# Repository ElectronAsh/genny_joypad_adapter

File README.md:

# genny_joypad_adapter
Genesis / MD joypad adapter for old-skool computers and consoles.

WARNING: Please do not use this adapter yet!

It's still a work-in-progress, and damage may occur to both the console / computer and the joypad.

The resistors should limit the maximum current on each signal pin, and it should in theory work on the "Atari style" joystick ports, 
on machines like the Atari 2600/400/800/1200/130XE/ST, Amiga, Vic 20, C64 / C64GS etc.

The diodes allow the Genesis joypad to only pull the signals LOW on the computer side.

The DIP switches are for enabling two-button support for the Atari 7800.

DIP switch 1 enables connection of pin 6, which is normally the "Fire" button on many retro machines.

DIP switches 2 and 3 allow the PNP transistors to drive pins 9 and 5 HIGH, as those are Active-High on the 7800.
Buttons B and C on the Genesis joypad can then be used as "Left Button" / "Right Button" (respectively) on the 7800.

All DIP switches should be OFF when the adapter is used with machines other than the Atari 7800.

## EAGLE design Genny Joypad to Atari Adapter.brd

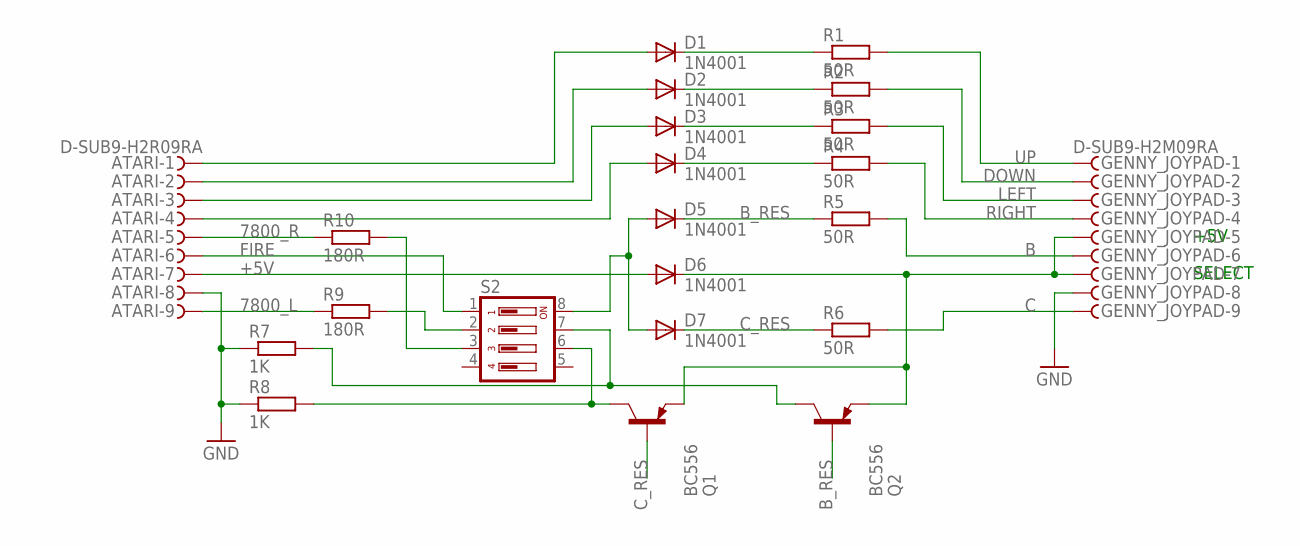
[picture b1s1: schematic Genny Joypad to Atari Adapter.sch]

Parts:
ATARI: D-SUB9-H2R09RA; H2R09RA
D1, D2, D3, D4, D5, D6, D7: 1N4001; DO35-7
GENNY_JOYPAD: D-SUB9-H2M09RA; H2M09RA
Q1, Q2: BC556; TO92-EBC
R1, R2, R3, R4, R5, R6: 50R; 0204/7
R7, R8: 1K; 0204/7
R9, R10: 180R; 0204/7
S2: DIP04YL

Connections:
7800_L: ATARI.9, R9.1
7800_R: ATARI.5, R10.1
+5V: D6.C, GENNY_JOYPAD.5, GENNY_JOYPAD.7, Q1.E, Q2.E
B: GENNY_JOYPAD.6, R5.2
B_PNP: Q2.C, R7.2, S2.7
B_RES: D5.C, Q2.B, R5.1
C: GENNY_JOYPAD.9, R6.2
C_PNP: Q1.C, R8.2, S2.6
C_RES: D7.C, Q1.B, R6.1
DOWN: GENNY_JOYPAD.2, R2.2
FIRE: D5.A, D7.A, S2.8
GND: ATARI.8, GENNY_JOYPAD.8, R7.1, R8.1
LEFT: GENNY_JOYPAD.3, R3.2
unnamed: D1.C, R1.1
unnamed: ATARI.7, D6.A
unnamed: ATARI.1, D1.A
unnamed: D2.C, R2.1
unnamed: ATARI.2, D2.A
unnamed: D3.C, R3.1
unnamed: ATARI.3, D3.A
unnamed: D4.C, R4.1
unnamed: ATARI.4, D4.A
unnamed: ATARI.6, S2.1
unnamed: R9.2, S2.2
unnamed: R10.2, S2.3
RIGHT: GENNY_JOYPAD.4, R4.2
UP: GENNY_JOYPAD.1, R1.2

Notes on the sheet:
+5V
SELECT

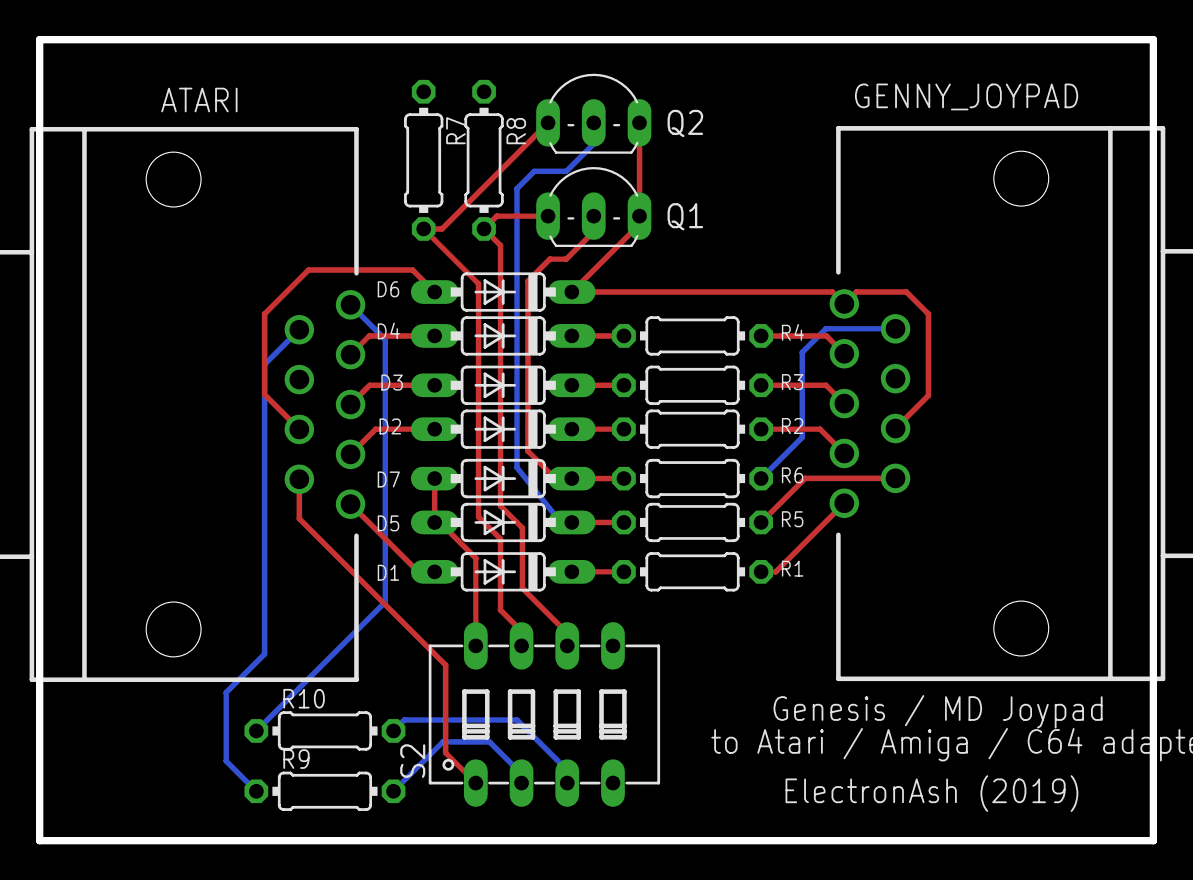
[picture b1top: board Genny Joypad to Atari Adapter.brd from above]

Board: 2 copper layers, 61.9 x 44.5 mm, 22 parts (0 on the bottom side), 27 nets.
